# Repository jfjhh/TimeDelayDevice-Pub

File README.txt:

Time Delay Device Documentation
===============================

See `./doc/doc-all.pdf`. It's header is reproduced below.

All of the documentation concerning the auxilliary files for the project
is assembled here. What follows is a description of the contents of each
directory.

-   `adjustable-delay`: Schematics and ideas for implementing adjustable
    delay in the circuit. The subdirectory `Linear` contains a tenative
    schematic (KiCAD files and <span
    style="font-variant:small-caps;">pdf</span>) of a circuit that
    implements the different clock frequencies by counting, while
    `Arbitrary` gives what I have so far in creating an arbitrary delay
    circuit.

-   `arduino`: The code uploaded to the Arduino Due.

-   `characterization`: Contains many different parts of the code used
    to analyze the characterization data for the device, and includes
    instructions on how to program the history.

-   `doc`: The top-level documentation directory (this one).

-   `fifo-p3f`: The KiCAD files for the device, as well as a schematic
    <span style="font-variant:small-caps;">pdf</span> and the gerber
    files that I sent for manufacture.

-   `figures`: The images and GNUPlot code used to create the figures
    for the paper.[^1]

-   `program-rescaling`: The code used to calculate the gain and offset
    resistor values to be optimal, given the constraints of E-series
    values and the overall resistances needed.

-   `triangle`: The code used to generate the spumpus (initial history
    signal) for the triangle-<span
    style="font-variant:small-caps;">dde</span> (relay-control) circuit
    in the paper. This is a good starting point if you want to program
    something different.

[^1]: *Spumpus* stands for spiky lumpus, where *lumpus* refers to a
    lumpy-looking signal. We want a strange signal for the programming
    to demonstrate that it is really *arbitrary*.

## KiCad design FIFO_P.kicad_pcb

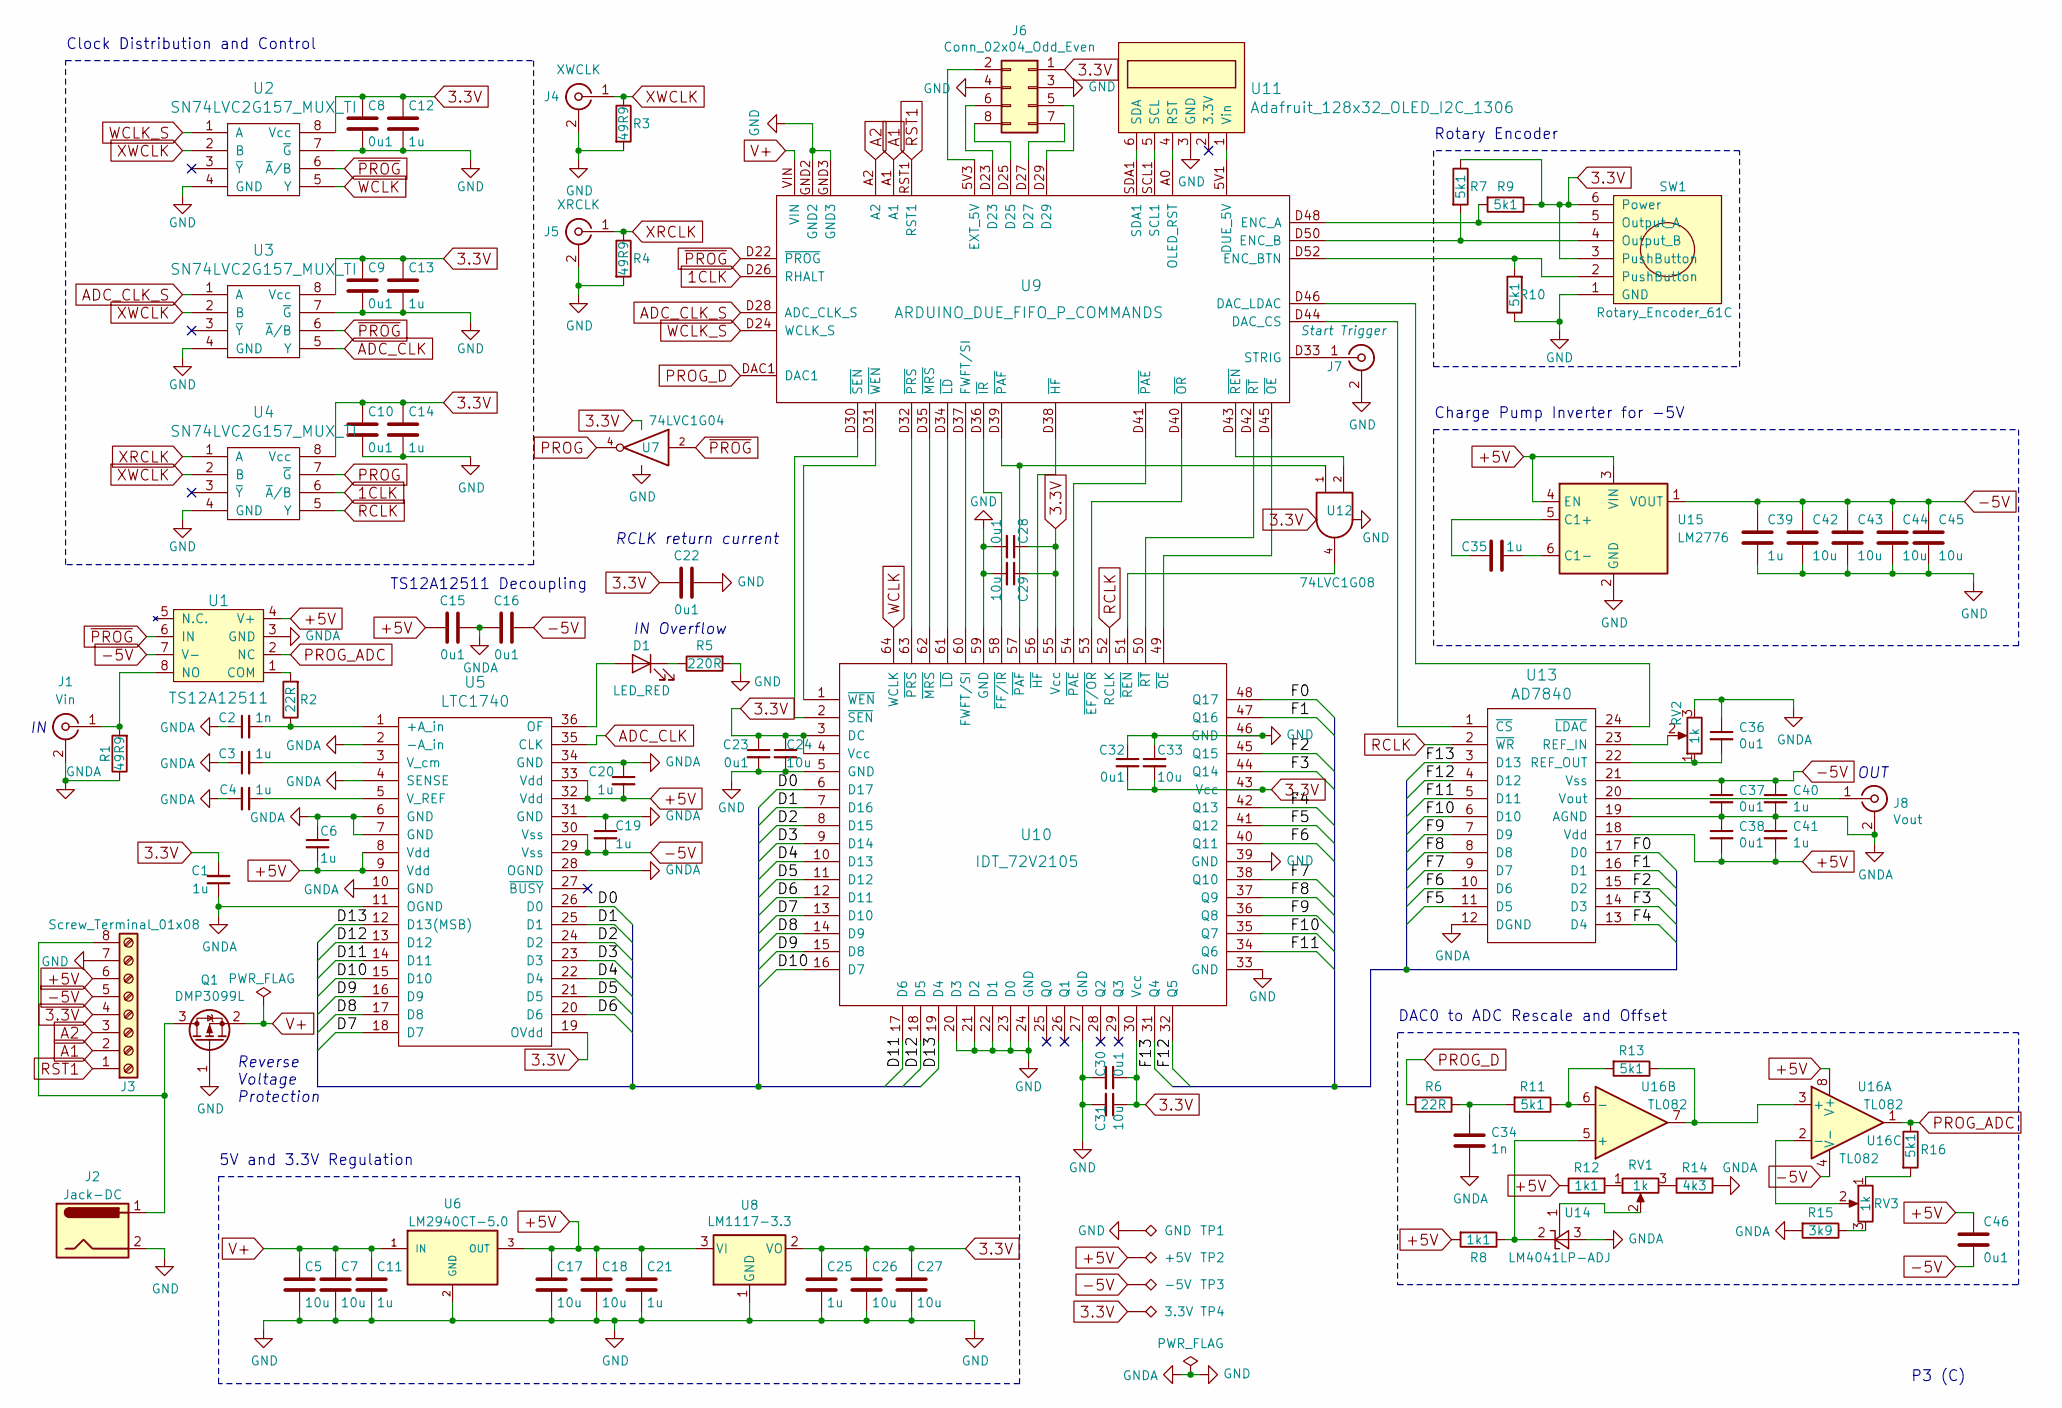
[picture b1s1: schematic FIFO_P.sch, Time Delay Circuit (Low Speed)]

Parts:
C1, C3, C4, C6, C11, C12, C13, C14, C19, C20, C21, C25, C35, C39, C40, C41: 1u; C_0805_2012Metric_Pad1.15x1.40mm_HandSolder
C2, C34: 1n; C_0805_2012Metric_Pad1.15x1.40mm_HandSolder
C5, C7, C17, C18, C24, C26, C27, C29, C31, C33, C42, C43, C44, C45: 10u; C_0805_2012Metric_Pad1.15x1.40mm_HandSolder
C8, C9, C10, C15, C16, C22, C23, C28, C30, C32, C36, C37, C38, C46: 0u1; C_0805_2012Metric_Pad1.15x1.40mm_HandSolder
D1: LED_RED; LED_D3.0mm
J1: Vin; BNC_TEConnectivity_1478204_Vertical
J2: Jack-DC; BarrelJack_Horizontal
J3: Screw_Terminal_01x08; TerminalBlock_Phoenix_MKDS-3-8-5.08_1x08_P5.08mm_Horizontal
J4: XWCLK; BNC_TEConnectivity_1478204_Vertical
J5: XRCLK; BNC_TEConnectivity_1478204_Vertical
J6: Conn_02x04_Odd_Even; PinSocket_2x04_P1.27mm_Vertical
J7: Start Trigger; BNC_TEConnectivity_1478204_Vertical
J8: Vout; BNC_TEConnectivity_1478204_Vertical
Q1: DMP3099L; SOT-23
R1, R3, R4: 49R9; R_0805_2012Metric_Pad1.15x1.40mm_HandSolder
R2, R6: 22R; R_0805_2012Metric_Pad1.15x1.40mm_HandSolder
R5: 220R; R_0805_2012Metric_Pad1.15x1.40mm_HandSolder
R7, R9, R10, R11, R13, R16: 5k1; R_0805_2012Metric_Pad1.15x1.40mm_HandSolder
R8, R12: 1k1; R_0805_2012Metric_Pad1.15x1.40mm_HandSolder
R14: 4k3; R_0805_2012Metric_Pad1.15x1.40mm_HandSolder
R15: 3k9; R_0805_2012Metric_Pad1.15x1.40mm_HandSolder
RV1, RV3: 1k; Potentiometer_Vishay_TS53YL_Vertical
RV2: 1k; Potentiometer_Bourns_3296W_Vertical
SW1: Rotary_Encoder_61C
TP1: GND; Test_Pin
TP2: +5V; Test_Pin
TP3: -5V; Test_Pin
TP4: 3.3V; Test_Pin
U1: TS12A12511; SOT-23-8_Handsoldering
U2, U3, U4: SN74LVC2G157_MUX_TI; SSOP-8_2.95x2.8mm_P0.65mm
U5: LTC1740; SSOP-36_5.3mm_Pitch0.65mm
U6: LM2940CT-5.0; TO-220-3_Horizontal_TabDown
U7: 74LVC1G04; SOT-23-5_HandSoldering
U8: LM1117-3.3; TO-252-3_TabPin2
U9: ARDUINO_DUE_FIFO_P_COMMANDS; Arduino_Due_Selected_Pins
U10: IDT_72V2105; LQFP-64_14x14mm_P0.8mm_HandSolder
U11: Adafruit_128x32_OLED_I2C_1306
U12: 74LVC1G08; SOT-23-5_HandSoldering
U13: AD7840; SSOP-24_5.3x8.2mm_P0.65mm
U14: LM4041LP-ADJ; SOT-23_Handsoldering
U15: LM2776; SOT-23-6
U16: TL082; SOIC-8_3.9x4.9mm_P1.27mm

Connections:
1CLK: U4.6 (~A~/B~), U9.D26 (RHALT)
3.3V: C1.2, C8.1, C9.1, C10.1, C12.1, C13.1, C14.1, C22.1, C23.1, C24.1, C25.1, C26.1, C27.1, C28.1, C29.1, C30.1, C31.1, C32.2, C33.2, J3.4, J6.1, R7.1, R9.1, SW1.3 (PushButton), SW1.6 (Power), TP4.1, U2.8 (Vcc), U3.8 (Vcc), U4.8 (Vcc), U5.19 (OVdd), U7.5 (VCC), U8.2 (VO), U10.3 (DC), U10.4 (Vcc), U10.30 (Vcc), U10.43 (Vcc), U10.55 (Vcc), U12.5 (VCC)
+5V: C6.2, C15.1, C17.1, C18.1, C20.2, C21.1, C38.2, C41.2, C46.1, J3.6, R8.2, R12.1, TP2.1, U1.4 (V+), U5.8 (Vdd), U5.9 (Vdd), U5.32 (Vdd), U5.33 (Vdd), U6.3 (OUT), U8.3 (VI), U13.18 (Vdd), U15.3 (VIN), U15.4 (EN), U16.8 (V+)
-5V: C16.2, C19.2, C37.1, C39.1, C40.1, C42.1, C43.1, C44.1, C45.1, C46.2, J3.5, TP3.1, U1.7 (V-), U5.29 (Vss), U5.30 (Vss), U13.21 (Vss), U15.1 (VOUT), U16.4 (V-)
/D0: U5.26 (D0), U10.6 (D17)
/D1: U5.25 (D1), U10.7 (D16)
/D2: U5.24 (D2), U10.8 (D15)
/D3: U5.23 (D3), U10.9 (D14)
/D4: U5.22 (D4), U10.10 (D13)
/D5: U5.21 (D5), U10.11 (D12)
/D6: U5.20 (D6), U10.12 (D11)
/D7: U5.18 (D7), U10.13 (D10)
/D8: U5.17 (D8), U10.14 (D9)
/D9: U5.16 (D9), U10.15 (D8)
/D10: U5.15 (D10), U10.16 (D7)
/D11: U5.14 (D11), U10.17 (D6)
/D12: U5.13 (D12), U10.18 (D5)
/D13: U5.12 (D13(MSB)), U10.19 (D4)
/F0: U10.48 (Q17), U13.17 (D0)
/F1: U10.47 (Q16), U13.16 (D1)
/F2: U10.45 (Q15), U13.15 (D2)
/F3: U10.44 (Q14), U13.14 (D3)
/F4: U10.42 (Q13), U13.13 (D4)
/F5: U10.41 (Q12), U13.11 (D5)
/F6: U10.40 (Q11), U13.10 (D6)
/F7: U10.38 (Q10), U13.9 (D7)
/F8: U10.37 (Q9), U13.8 (D8)
/F9: U10.36 (Q8), U13.7 (D9)
/F10: U10.35 (Q7), U13.6 (D10)
/F11: U10.34 (Q6), U13.5 (D11)
/F12: U10.32 (Q5), U13.4 (D12)
/F13: U10.31 (Q4), U13.3 (D13)
A1: J3.2, U9.A1
A2: J3.3, U9.A2
ADC_CLK: U3.5 (Y), U5.35 (CLK)
ADC_CLK_S: U3.1 (A), U9.D28 (ADC_CLK_S)
GND: C1.1, C2.1, C3.1, C4.2, C5.2, C6.1, C7.2, C8.2, C9.2, C10.2, C11.2, C12.2, C13.2, C14.2, C15.2, C16.1, C17.2, C18.2, C19.1, C20.1, C21.2, C22.2, C23.2, C24.2, C25.2, C26.2, C27.2, C28.2, C29.2, C30.2, C31.2, C32.1, C33.1, C34.2, C36.1, C37.2, C38.1, C39.2, C40.2, C41.1, C42.2, C43.2, C44.2, C45.2, J1.2 (Ext), J2.2, J3.7, J4.2 (Ext), J5.2 (Ext), J6.3, J6.4, J7.2 (Ext), J8.2 (Ext), Q1.1 (G), R1.1, R3.2, R4.2, R5.2, R10.1, R14.2, R15.2, RV2.3, SW1.1 (GND), TP1.1, U1.3 (GND), U2.4 (GND), U2.7 (~G), U3.4 (GND), U3.7 (~G), U4.4 (GND), U5.2 (-A_in), U5.4 (SENSE), U5.6 (GND), U5.7 (GND), U5.10 (GND), U5.11 (OGND), U5.28 (OGND), U5.31 (GND), U5.34 (GND), U6.2 (GND), U7.3 (GND), U8.1 (GND), U9.GND2, U9.GND3, U10.5 (GND), U10.20 (D3), U10.21 (D2), U10.22 (D1), U10.23 (D0), U10.24 (GND), U10.27 (GND), U10.33 (GND), U10.39 (GND), U10.46 (GND), U10.59 (GND), U11.3 (GND), U12.3 (GND), U13.12 (DGND), U13.19 (AGND), U14.3 (A), U15.2 (GND)
unnamed: C2.2, R2.1, U5.1 (+A_in)
unnamed: C3.2, U5.3 (V_cm)
unnamed: C4.1, U5.5 (V_REF)
unnamed: C34.1, R6.1, R11.2
unnamed: C35.1, U15.6 (C1-)
unnamed: C35.2, U15.5 (C1+)
unnamed: C36.2, RV2.1, U13.22 (REF_OUT)
unnamed: D1.1 (K), R5.1
unnamed: D1.2 (A), U5.36 (OF)
unnamed: J1.1 (In), R1.2, U1.8 (NO)
unnamed: J2.1, J3.8, Q1.3 (D)
unnamed: J6.2, U9.5V3 (EXT_5V)
unnamed: J6.5, U9.D29
unnamed: J6.6, U9.D23
unnamed: J6.7, U9.D27
unnamed: J6.8, U9.D25
unnamed: J7.1 (In), U9.D33 (STRIG)
unnamed: J8.1 (In), U13.20 (Vout)
unnamed: R2.2, U1.1 (COM)
unnamed: R7.2, SW1.4 (Output_B), U9.D50 (ENC_B)
unnamed: R8.1, U14.2 (K), U16.5 (+)
unnamed: R9.2, SW1.5 (Output_A), U9.D48 (ENC_A)
unnamed: R10.2, SW1.2 (PushButton), U9.D52 (ENC_BTN)
unnamed: R11.1, R13.2, U16.6 (-)
unnamed: R12.2, RV1.1
unnamed: R13.1, U16.3 (+), U16.7
unnamed: R14.1, RV1.3
unnamed: R15.1, RV3.3
unnamed: R16.2, RV3.1
unnamed: RV1.2, U14.1 (FB)
unnamed: RV2.2, U13.23 (REF_IN)
unnamed: RV3.2, U16.2 (-)
unnamed: U9.D31 (~WEN), U10.1 (~WEN)
unnamed: U9.D30 (~SEN), U10.2 (~SEN)
unnamed: U9.D45 (~OE), U10.49 (~OE)
unnamed: U9.D42 (~RT), U10.50 (~RT)
unnamed: U10.51 (~REN), U12.4
unnamed: U9.D40 (~OR), U10.53 (~EF/OR)
unnamed: U9.D41 (~PAE), U10.54 (~PAE)
unnamed: U9.D38 (~HF), U10.56 (~HF)
unnamed: U9.D39 (~PAF), U10.57 (~PAF), U12.1
unnamed: U9.D36 (~IR), U10.58 (~FF/IR)
unnamed: U9.D37 (FWFT/SI), U10.60 (FWFT/SI)
unnamed: U9.D34 (~LD), U10.61 (~LD)
unnamed: U9.D35 (~MRS), U10.62 (~MRS)
unnamed: U9.D32 (~PRS), U10.63 (~PRS)
unnamed: U9.5V1 (DUE_5V), U11.1 (Vin)
unnamed: U9.A0 (OLED_RST), U11.4 (RST)
unnamed: U9.SCL1, U11.5 (SCL)
unnamed: U9.SDA1, U11.6 (SDA)
unnamed: U9.D43 (~REN), U12.2
unnamed: U9.D44 (DAC_CS), U13.1 (~CS)
unnamed: U9.D46 (DAC_LDAC), U13.24 (~LDAC)
PROG: U4.7 (~G), U7.4
PROG_ADC: R16.1, U1.2 (NC), U16.1
PROG_D: R6.2, U9.DAC1
RCLK: U4.5 (Y), U10.52 (RCLK), U13.2 (~WR)
RST1: J3.1, U9.RST1
V+: C5.1, C7.1, C11.1, Q1.2 (S), U6.1 (IN), U9.VIN
WCLK: U2.5 (Y), U10.64 (WCLK)
WCLK_S: U2.1 (A), U9.D24 (WCLK_S)
XRCLK: J5.1 (In), R4.1, U4.1 (A)
XWCLK: J4.1 (In), R3.1, U2.2 (B), U3.2 (B), U4.2 (B)
~PROG: U1.6 (IN), U2.6 (~A~/B~), U3.6 (~A~/B~), U7.2, U9.D22 (~PROG)

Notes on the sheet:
Rotary Encoder
P3 (C)
5V and 3.3V Regulation
Clock Distribution and Control
Charge Pump Inverter for -5V
DAC0 to ADC Rescale and Offset
TS12A12511 Decoupling
Reverse Voltage Protection
IN Overflow
OUT
RCLK return current

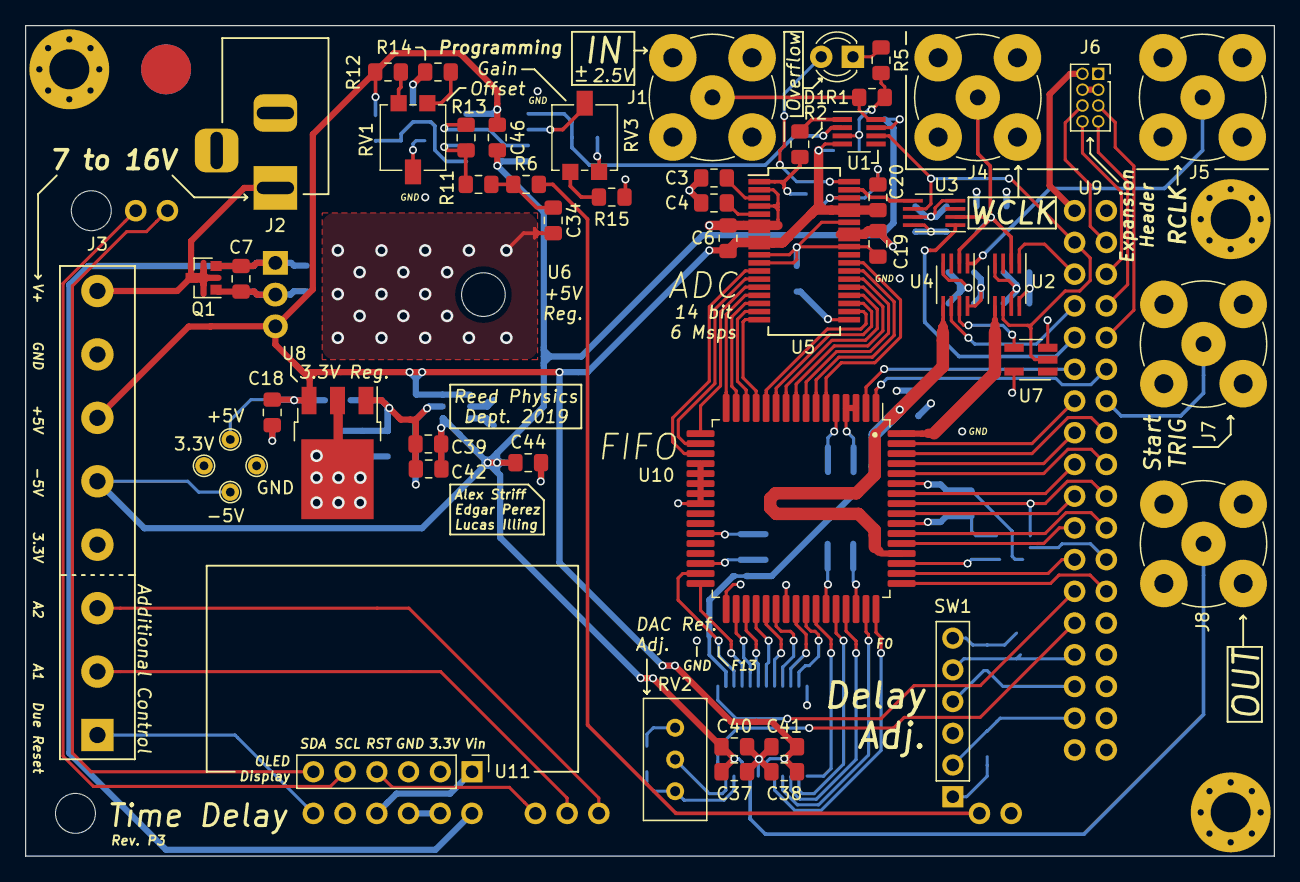
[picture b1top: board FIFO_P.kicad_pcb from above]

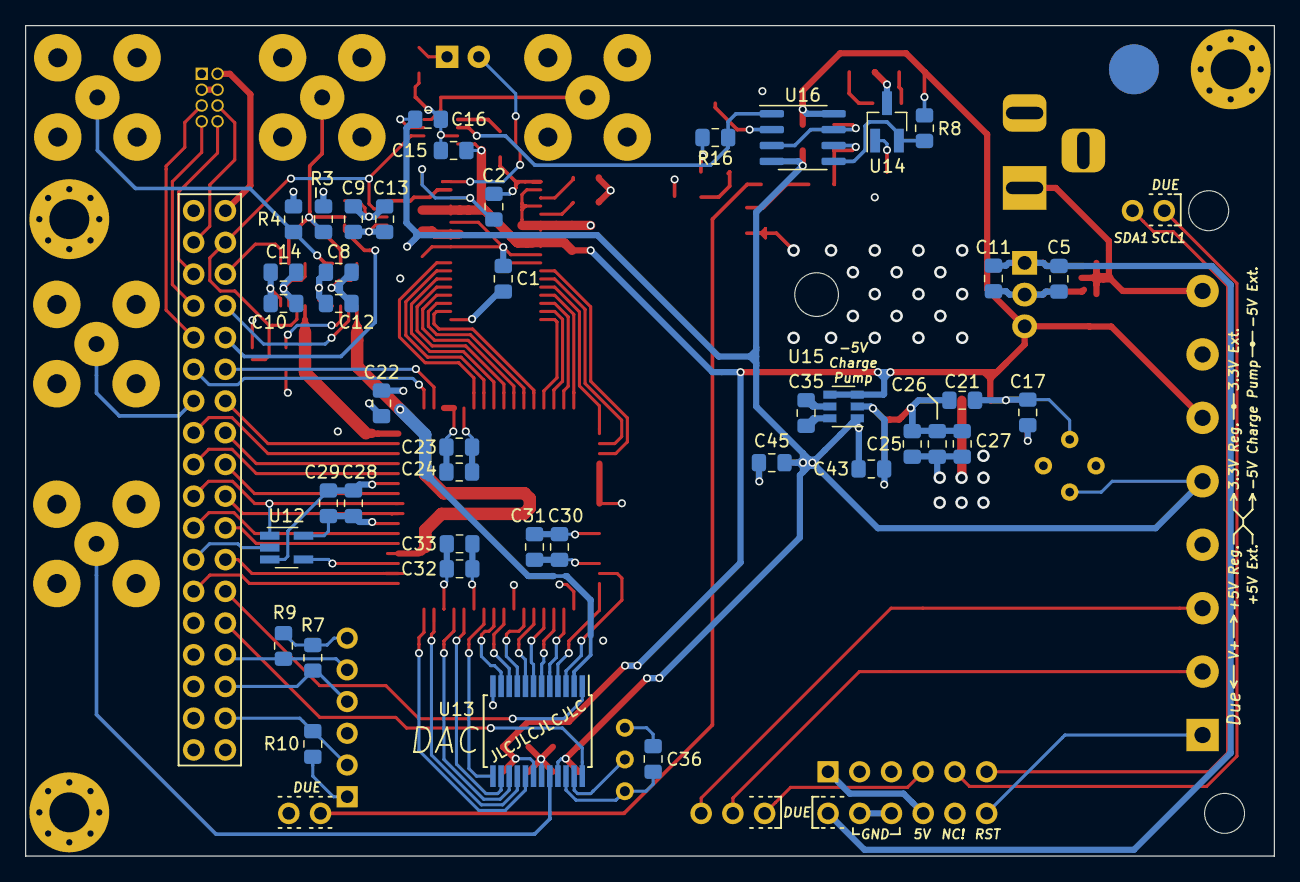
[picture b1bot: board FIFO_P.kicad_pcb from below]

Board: 4 copper layers, 100.0 x 66.5 mm, 96 parts (42 on the bottom side), 101 nets.

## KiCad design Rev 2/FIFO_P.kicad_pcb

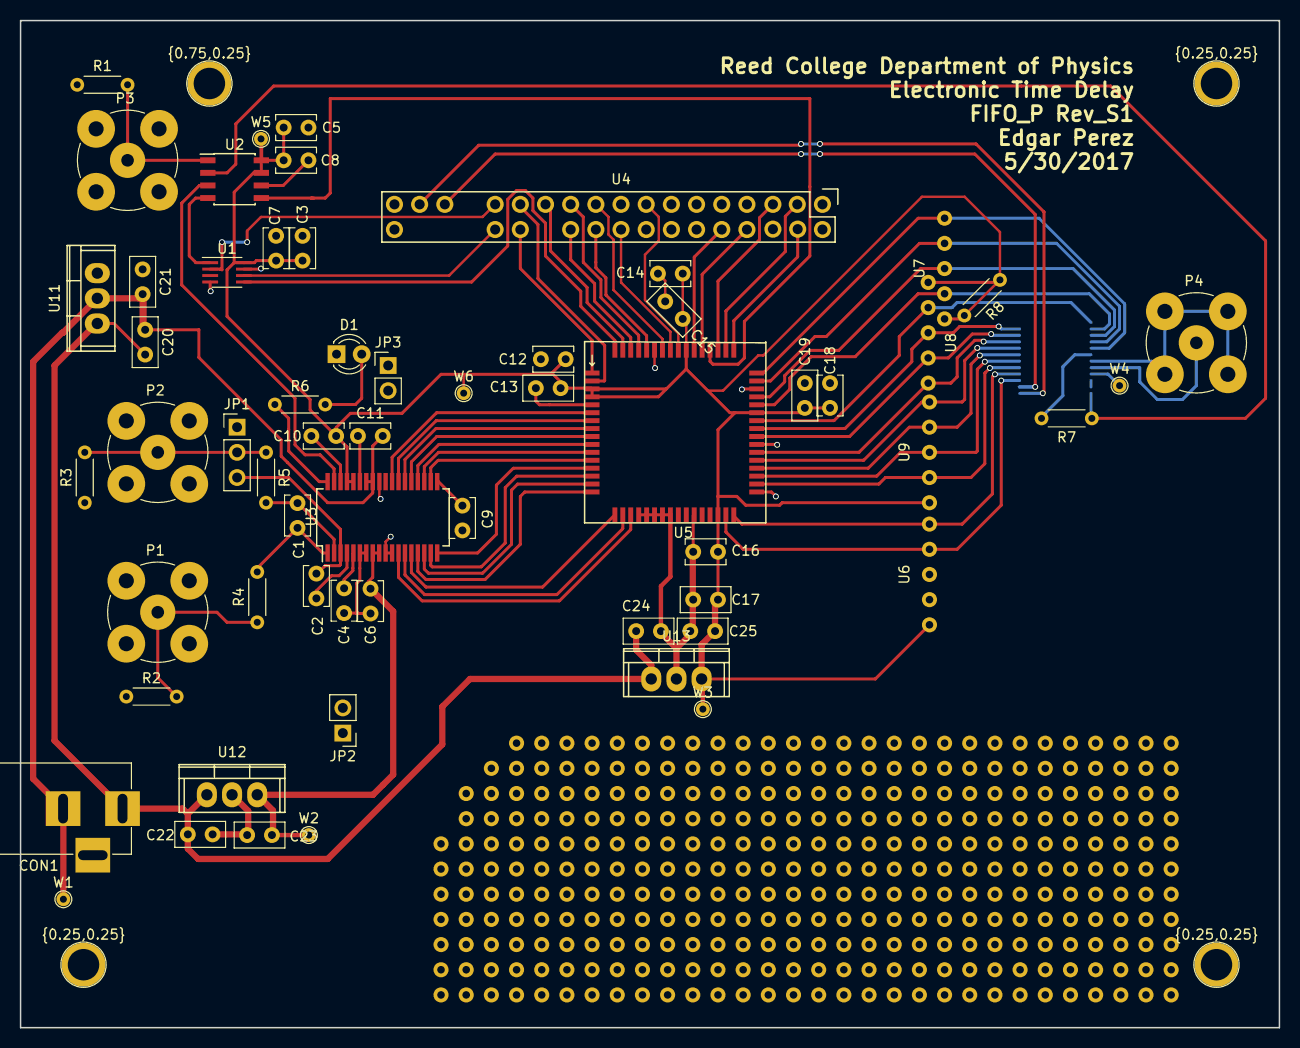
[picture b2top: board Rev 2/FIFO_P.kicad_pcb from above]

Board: 2 copper layers, 127.0 x 101.6 mm, 65 parts (1 on the bottom side), 69 nets.

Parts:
C1: 560pF; C_Rect_L4.0mm_W2.5mm_P2.50mm
C2, C4, C6, C7, C8, C9, C10, C11: 1uF; C_Rect_L4.0mm_W2.5mm_P2.50mm
C3, C5: 100nF; C_Rect_L4.0mm_W2.5mm_P2.50mm
C12, C14, C16, C18: .1uF; C_Rect_L4.0mm_W2.5mm_P2.50mm
C13, C15, C17, C19, C20, C21, C22, C23, C24, C25: 10uF; C_Disc_D5.0mm_W2.5mm_P2.50mm
CON1: BARREL_JACK
D1: LED; LED_D3.0mm
JP1: JUMPER3; Pin_Header_Straight_1x03_Pitch2.54mm
JP2, JP3: JUMPER; Pin_Header_Straight_1x02_Pitch2.54mm
P1: Vin +; bnc-ci
P2: Vin -; bnc-ci
P3: CLK; bnc-ci
P4: Vout; bnc-ci
R1: 50; R_Axial_DIN0204_L3.6mm_D1.6mm_P5.08mm_Horizontal
R2, R3, R4: 51R; R_Axial_DIN0204_L3.6mm_D1.6mm_P5.08mm_Horizontal
R5, R8: 0; R_Axial_DIN0204_L3.6mm_D1.6mm_P5.08mm_Horizontal
R6: 500R; R_Axial_DIN0204_L3.6mm_D1.6mm_P5.08mm_Horizontal
R7: 100k; R_Axial_DIN0204_L3.6mm_D1.6mm_P5.08mm_Horizontal
U1: SN74LVC2G157_MUX_TI; SSOP-8_2.95x2.8mm_Pitch0.65mm
U2: IDT_ICS551; SOIC-8_3.9x4.9mm_Pitch1.27mm
U3: LTC1740; SSOP-36_5.3mm_Pitch0.65mm
U4: ARDUINO_DUE_FIFO_P_COMMANDS; Arduino_DUE_2x18
U5: IDT_72V2105; FIFO_IDT_72V2105_L10PFG
U6, U7, U8, U9: R_Bussed_4Pack; SIP_5
U10: AD7840; SSOP-24_5.3x8.2mm_Pitch0.65mm
U11, U12: LM2940CT-5.0; TO-220
U13: LM2940CT-3.3; TO-220
W1, W2, W3, W4, W5, W6: TEST_1P; Test_Pin
{0.25,0.25}, {0.25,0.25}#2, {0.25,0.25}#3, {0.75,0.25}: 1pin

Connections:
3.3V: C3.2, C5.1, C7.2, C8.1, C9.2, C10.2, C12.1, C13.1, C14.1, C15.1, C16.1, C17.1, C18.2, C19.2, C25.2, R8.1, R8.2, U1.8, U2.7, U2.8, U3.19, U3.32, U3.33, U5.3, U5.4, U5.30, U5.43, U5.55, U6.5, U7.5, U8.5, U9.5, U13.3, W3.1, W5.1, W6.1
+5V: C6.2, C23.2, R7.1, U3.8, U3.9, U10.18, U12.3, W2.1
+12V: C20.2, C22.1, C24.1, CON1.1, U11.1, U12.1, U13.1
-5V: C11.2, C20.1, C21.2, CON1.2, U3.29, U3.30, U10.21, U11.2, W1.1, W4.1
CLK: U2.3, U3.35
CLK1: U1.1, U2.4
GND: C3.1, C5.2, C7.1, C8.2, C9.1, C12.2, C13.2, C14.2, C15.2, C16.2, C17.2, C18.1, C19.1, C21.1, C22.2, C23.1, C24.2, C25.1, D1.1, JP2.1, JP3.1, P3.2, R1.2, U1.4, U1.7, U2.6, U3.10, U3.11, U3.28, U4.GND, U5.5, U5.20, U5.21, U5.22, U5.23, U5.24, U5.27, U5.33, U5.39, U5.46, U5.59, U10.12, U11.3, U12.2, U13.2
GNDA: C2.1, C4.2, C6.1, C10.1, C11.1, JP1.1, JP2.2, JP3.2, P1.2, P2.2, R2.1, R3.1, U3.4, U3.6, U3.7, U3.31, U3.34
LDAC: R7.2, U2.2, U10.24
unnamed: C1.1, R4.2, U3.1
unnamed: C1.2, R5.2, U3.2
unnamed: C2.2, JP1.3, U3.3
unnamed: C4.1, U3.5
unnamed: D1.2, R6.2
unnamed: JP1.2, P2.1, R3.2, R5.1
unnamed: P1.1, R2.2, R4.1
unnamed: P3.1, R1.1, U2.1
unnamed: P4.1, U10.20
unnamed: P4.2, U10.19
unnamed: R6.1, U3.36
unnamed: U3.12, U5.19
unnamed: U3.13, U5.18
unnamed: U3.14, U5.17
unnamed: U3.15, U5.16
unnamed: U3.16, U5.15
unnamed: U3.17, U5.14
unnamed: U3.18, U5.13
unnamed: U3.20, U5.12
unnamed: U3.21, U5.11
unnamed: U3.22, U5.10
unnamed: U3.23, U5.9
unnamed: U3.24, U5.8
unnamed: U3.25, U5.7
unnamed: U3.26, U5.6
unnamed: U4.22, U5.50
unnamed: U4.23, U5.49
unnamed: U4.24, U5.51
unnamed: U4.27, U5.53
unnamed: U4.29, U5.54
unnamed: U4.34, U5.56
unnamed: U4.37, U5.57
unnamed: U4.38, U5.58
unnamed: U4.39, U5.60
unnamed: U4.40, U5.61
unnamed: U4.41, U5.62
unnamed: U4.42, U5.63
unnamed: U4.44, U5.2
unnamed: U4.45, U5.1
unnamed: U4.52, U10.1
unnamed: U4.50, U10.2
unnamed: U5.31, U6.2, U10.3
unnamed: U5.32, U6.1, U10.4
unnamed: U5.34, U9.4, U10.5
unnamed: U5.35, U9.3, U10.6
unnamed: U5.36, U9.2, U10.7
unnamed: U5.37, U9.1, U10.8
unnamed: U5.38, U8.1, U10.9
unnamed: U5.40, U8.2, U10.10
unnamed: U5.41, U8.3, U10.11
unnamed: U5.42, U8.4, U10.13
unnamed: U5.44, U7.4, U10.14
unnamed: U5.45, U7.3, U10.15
unnamed: U5.47, U7.2, U10.16
unnamed: U5.48, U7.1, U10.17
unnamed: U10.22, U10.23
RCLK: U2.5, U5.52
WCLK: U1.5, U5.64
WCLK_S: U1.2, U4.46
WLSTN: U1.6, U4.47

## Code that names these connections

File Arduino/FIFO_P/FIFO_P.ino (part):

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// Clock control pin mappings:
// Active HIGH unless stated otherwise
pin nPROG  = 22;
pin CLK1   = 26; // 1CLK (single-clock operation)
pin WCLK_S = 24;
pin ADC_CLK_S = 28;
pin PROG_D = DAC1;
pin STRIG  = 33;

// FIFO flags to show in status. All active low.
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
    // Due (self) DAC initialization
    analogWriteResolution(12);
    pinMode(PROG_D, OUTPUT);
    analogWrite(PROG_D, 1u << (12 - 2)); // Half full scale

    // Clock control pins
    pinMode(nPROG,     OUTPUT);
    pinMode(CLK1,      OUTPUT);
    pinMode(WCLK_S,    OUTPUT);
    pinMode(ADC_CLK_S, OUTPUT);
    pinMode(STRIG,     OUTPUT);

    // Clock default state (single clock, not programming)
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
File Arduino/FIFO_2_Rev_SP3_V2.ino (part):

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const int OE = 23;
const int RT = 22;
const int REN = 24;
const int RCLK = 25;
const int RM = 26;
const int OR = 27;
const int PFM = 28;
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const int LD = 40;
const int MRS = 41;
const int PRS = 42;
// note the reassignment of the wclk and rlstn pin numbers. This was done make
// make the board routing possible.
// RLSTN was not being used anyway.
const int WCLK = 46;
const int WEN = 45;
const int SEN = 44;
const int WLSTN = 47;
const int RLSTN = 43;

// ADC PIN MAPPINGmm
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	pinMode(OE, OUTPUT);
	pinMode(RT, OUTPUT);
	pinMode(REN, INPUT);
	pinMode(RCLK, OUTPUT);
	pinMode(RM, OUTPUT);
	pinMode(OR, INPUT_PULLUP);
	pinMode(PFM, OUTPUT);
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	pinMode(LD, OUTPUT);
	pinMode(MRS, OUTPUT);
	pinMode(PRS, OUTPUT);
	pinMode(WCLK, OUTPUT);
	pinMode(WEN, OUTPUT);
	pinMode(SEN, OUTPUT);
	pinMode(WLSTN, OUTPUT);
	pinMode(RLSTN, OUTPUT);

	// SETTING UP DEFAULT STATES
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
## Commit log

2019-06-18 Initial upload
    Contains working files with no external dependencies. Rev 3 not included
2019-06-19 Fixed footprints; deleted PCB.
2019-06-19 Created 4-layer PCB
2019-06-19 Fix arduino header, started laying out connectors
    The pins used were changed, so the old code must be rewritten to use the new pins and port D instead of port A.
2019-06-20 ADC to FIFO routing
2019-06-22 Most routing done
2019-06-24 Added inverter for -5V
2019-06-24 Partial jumpers
2019-06-25 Cleanup; prepared to route header
2019-06-25 Routed FIFO-DAC header
2019-06-25 Moved power
2019-06-26 Actually fixed power and clocks
    TODO: Flip arduino header and reroute
2019-06-26 Fixed Arduino mounting holes
2019-06-26 Started silkscreen
2019-06-26 Cleaned up old files
2019-06-26 Silkscreen cleaned up on both sides
2019-06-26 More tweaks
2019-06-27 Added screw terminal footprint
2019-06-27 Fixed RV refdes
2019-06-27 Fixed RCLK trace
2019-06-27 Fix ferrite soldermask
2019-06-27 Fixed FIFO pin
2019-06-27 Boop
2019-06-27 Cleaned up input limit silkscreen
2019-06-27 Add ADC specs
2019-06-28 Swapped RT and OE to be sensible
2019-06-29 Add original Arduino code
2019-06-29 Cleaned up Arduino code
2019-06-29 Renamed Arduino code to FIFO_P
2019-07-01 Routed SMT DAC
    Modified from after Edgar's changes
2019-07-02 Add _partial_ BOM, minor tweaks to PCB
2019-07-02 Final revision before manufacture
2019-07-03 Added Gerbers and locked Due on pcb
2019-07-03 Flipped pins and added digit control
    The digit control allows manipulation of the word count like frequency entry on many function generators.
2019-07-09 Started adding OLED display support
2019-07-10 Double-press for menu satisfactory
    TODO: write a pager for help / info menu entries?
2019-07-12 Minor setup tweaks for debugging
2019-07-12 Somewhere SCREEN is needed to function; TODO: fix
2019-07-15 Add FIFO status and put strings in flash
2019-07-16 Begin cleaning up schematic. FIFO-DAC area ripped up
2019-07-16 Updated missing footprints on schematic
2019-07-16 More schematic cleanup: reannotate and re-do footprints
2019-07-16 Added screw terminal; put some new IC footprints in place
2019-07-16 Flipped Due pins to be correct to actual
2019-07-17 More progress on final board
2019-07-17 Reannotated and replaced many components. Bypass capacitors everywhere.
2019-07-17 Remapped some Due pins; fixed FIFO output vias
2019-07-18 More work, idk what I even changed at this point... lots of stuff
2019-07-19 More work. TODO: Change muxes to clock ADC and both R/WCLKs, not RCLK and WCLK
2019-07-20 Finished DAC0 to ADC rescale circuit; rerouted power
2019-07-22 Calculated optimum DAC0 to ADC resistor values and fixed schematic
2019-07-23 Updated schematic for dual clock operation; Squished everything!
2019-07-23 Fixed Due power and added AND gate for FIFO ~RE
2019-07-24 Almost done routing!
2019-07-24 Done with main circuit. TODO: EXT header and input protection
2019-07-25 Board pretty much done. Cleaned up silkscreen
2019-07-25 Fixed 1CLK signal. Board complete.
2019-07-25 Fixed power in voltage and specified layer stackup
2019-07-25 Moved power connector for new Due header clearance
2019-07-25 Made expansion header smaller
2019-07-26 Final order PCB. Added Gerbers
2019-07-26 Updated schematic PDF and Arduino pin mappings
2019-07-26 Start work on history programming
2019-07-26 Added hexdump to debug serial loading
2019-07-26 Untested programming code complete
2019-07-26 Clock slope approximation plots: naive version
2019-07-28 Add GLAD module schematic
2019-07-30 Fix RV2 to be a bit more friendly to the DAC reference
2019-08-01 GLAD schematic PDF; Fixed RV2 to be a bit more friendly to the DAC reference
2019-08-02 Fix offset issue with menu.
2019-08-06 Corrected FIFO word limits
2019-08-07 Circuit fixes and debugging; Everything provisionally works
2019-08-10 Add characterization work so far
2019-08-12 Applying different filters to 5 MHz difference data
2019-08-14 Fixed serial programming and added CRC generation
2019-08-15 Output filter data and difference plots
2019-08-16 Removed extraneous menu items and "No I/O" message
2019-08-20 Draft figures
2019-08-20 Dumped data to plot
2019-08-21 Publication figures with gnuplot
2019-08-22 Colorized figures
2019-08-22 Add triangle history generation
2019-08-22 Added more zeros to triangle history
2019-08-22 Modified triangle history again
2019-08-22 Inverted the spumpus
2019-08-22 Added spumpus and lumpus data
2019-08-22 Created spumpus plot
2019-08-27 Made three versions of each plot (colorschemes)
2019-08-27 Moved KiCAD files to a subdirectory
2019-08-27 Renamed directories
2019-08-27 Added documentation
2019-09-23 Markdown README for GitHub
